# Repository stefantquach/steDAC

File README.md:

# SteDAC

Open source audio DAC project based on the ES9038Q2M DAC from ESS. Still WIP

# Credits
Logo art by @yumightaswell (Instagram)

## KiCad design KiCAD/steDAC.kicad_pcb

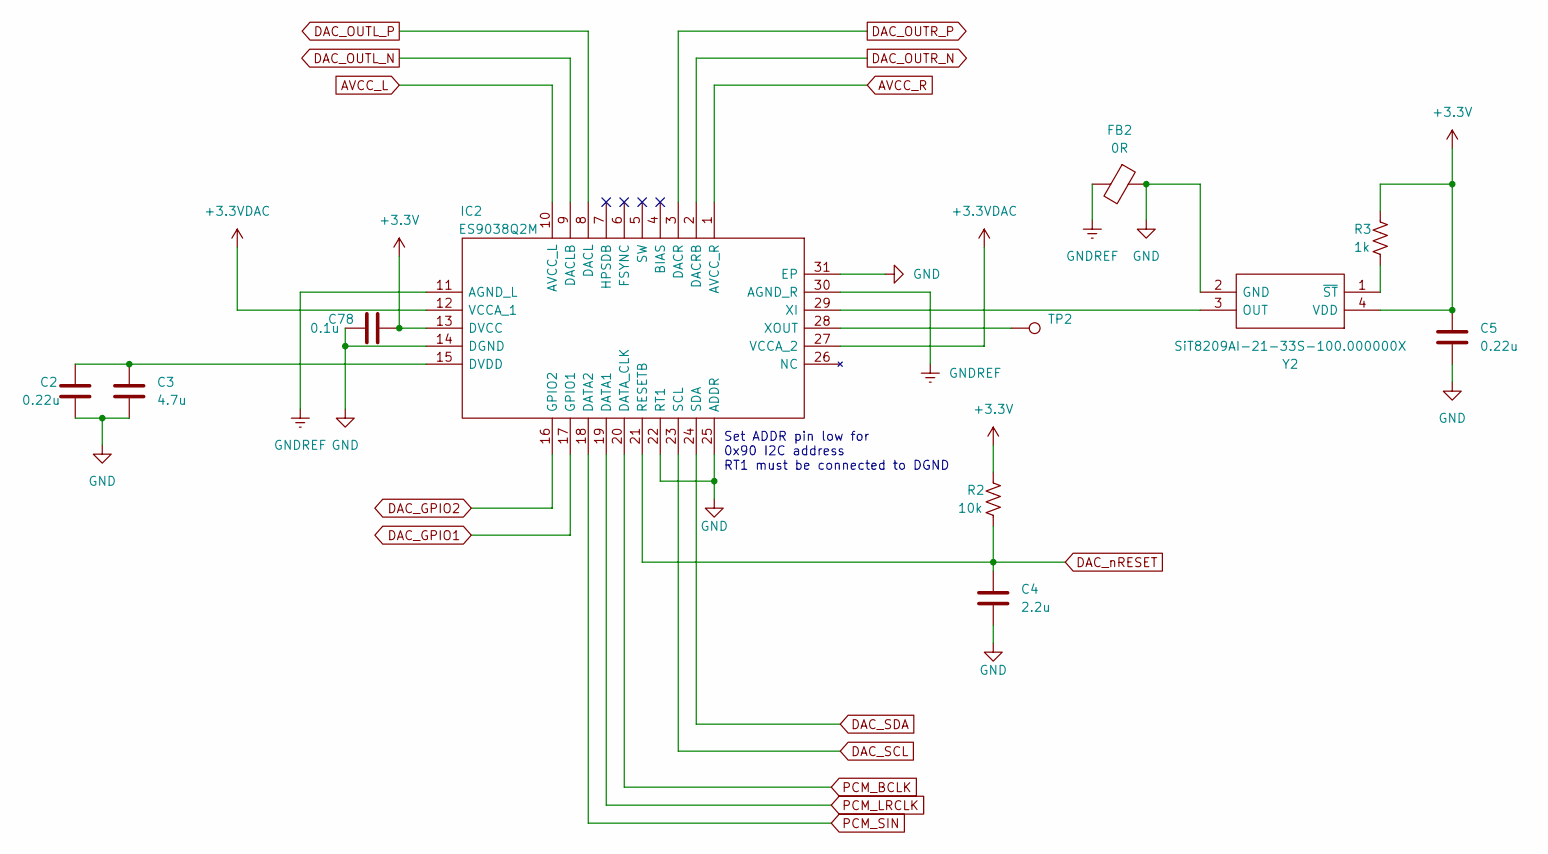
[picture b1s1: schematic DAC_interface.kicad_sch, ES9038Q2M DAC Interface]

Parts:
C2, C5: 0.22u; C_0805_2012Metric_Pad1.18x1.45mm_HandSolder; Part Number CL21B224KAFNNNG; Mouser Part Number 187-CL21B224KAFNNNG
C3: 4.7u; C_0805_2012Metric_Pad1.18x1.45mm_HandSolder; Part Number CC0805KKX5R7BB475; Mouser Part Number 603-CC805KKX5R7BB475
C4: 2.2u; C_0805_2012Metric_Pad1.18x1.45mm_HandSolder; Part Number TMK212B7225KGHT; Mouser Part Number 963-TMK212B7225KGHT
C78: 0.1u; C_0805_2012Metric_Pad1.18x1.45mm_HandSolder; Part Number CL21B104KBCNFNC; Mouser Part Number 187-CL21B104KBCNFNC
FB2: 0R; BEADC2012X110N; Part Number MFBW1V2012-000-R; Mouser Part Number 704-MFBW1V2012-000-R
IC2: ES9038Q2M; QFN40P300X500X80-31N-D; Manufacturer_Part_Number ES9038Q2M; Mouser Part Number 460-ES9038Q2M
R2: 10k; R_0805_2012Metric_Pad1.20x1.40mm_HandSolder; Part Number RC0805FR-7W10KL; Mouser Part Number 603-RC0805FR-7W10KL
R3: 1k; R_0805_2012Metric_Pad1.20x1.40mm_HandSolder; Part Number ERJ-HP6D1001V; Mouser Part Number 667-ERJ-HP6D1001V
TP2: TestPoint; TestPoint_Pad_D1.0mm
Y2: SiT8209AI-21-33S-100.000000X; SiT8209AI2133S100000000X; Manufacturer_Part_Number SiT8209AI-21-33S-100.000000X; Mouser Part Number 788-8209AI2133S-100X

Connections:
+3.3VDAC: IC2.12 (VCCA_1), IC2.27 (VCCA_2); also elsewhere on the board
+3V3: C5.1, C78.1, IC2.13 (DVCC), R2.1, R3.1, Y2.4 (VDD); also elsewhere on the board
AVCC_L: IC2.10 (AVCC_L); also elsewhere on the board
AVCC_R: IC2.1 (AVCC_R); also elsewhere on the board
DAC_GPIO1: IC2.17 (GPIO1); also elsewhere on the board
DAC_GPIO2: IC2.16 (GPIO2); also elsewhere on the board
DAC_OUTL_N: IC2.9 (DACLB); also elsewhere on the board
DAC_OUTL_P: IC2.8 (DACL); also elsewhere on the board
DAC_OUTR_N: IC2.2 (DACRB); also elsewhere on the board
DAC_OUTR_P: IC2.3 (DACR); also elsewhere on the board
DAC_SCL: IC2.23 (SCL); also elsewhere on the board
DAC_SDA: IC2.24 (SDA); also elsewhere on the board
DAC_nRESET: C4.1, IC2.21 (RESETB), R2.2; also elsewhere on the board
GND: C2.2, C3.2, C4.2, C5.2, C78.2, FB2.1, IC2.14 (DGND), IC2.22 (RT1), IC2.25 (ADDR), IC2.31 (EP), Y2.2 (GND); also elsewhere on the board
GNDREF: FB2.2, IC2.11 (AGND_L), IC2.30 (AGND_R); also elsewhere on the board
unnamed: C2.1, C3.1, IC2.15 (DVDD)
unnamed: IC2.28 (XOUT), TP2.1
unnamed: IC2.29 (XI), Y2.3 (OUT)
unnamed: R3.2, Y2.1 (~ST)
PCM_BCLK: IC2.20 (DATA_CLK); also elsewhere on the board
PCM_LRCLK: IC2.19 (DATA1); also elsewhere on the board
PCM_SIN: IC2.18 (DATA2); also elsewhere on the board

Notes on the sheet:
Set ADDR pin low for 0x90 I2C address RT1 must be connected to DGND

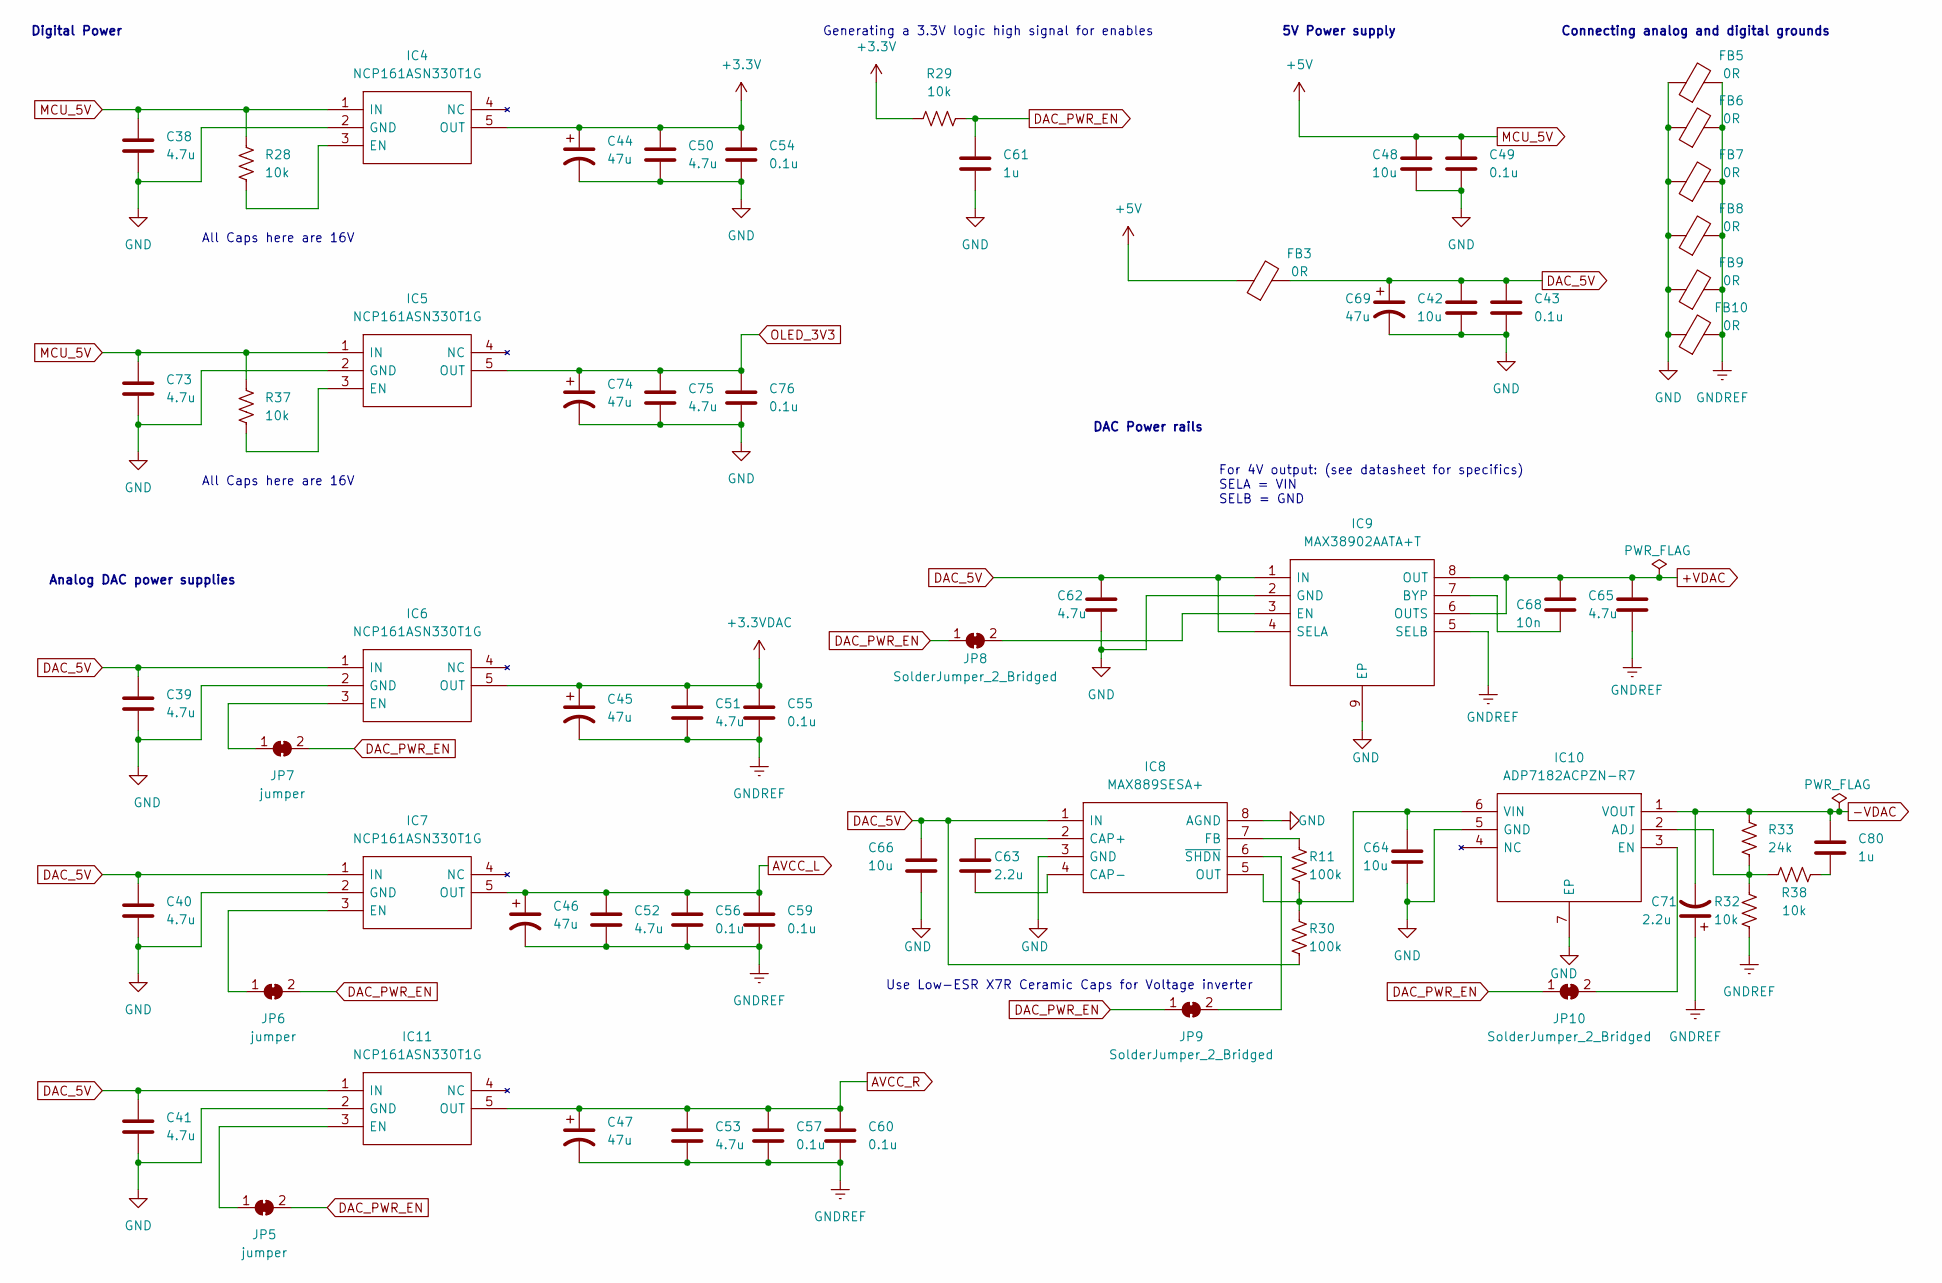
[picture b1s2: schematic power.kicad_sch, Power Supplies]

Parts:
C38, C39, C40, C41, C50, C51, C52, C53, C62, C65, C73, C75: 4.7u; C_0805_2012Metric_Pad1.18x1.45mm_HandSolder; Part Number CC0805KKX5R7BB475; Mouser Part Number 603-CC805KKX5R7BB475
C42, C48, C64, C66: 10u; C_0805_2012Metric_Pad1.18x1.45mm_HandSolder; Part Number TMK212BBJ106KG-T; Mouser Part Number 963-TMK212BBJ106KG-T
C43, C49, C54, C55, C56, C57, C59, C60, C76: 0.1u; C_0805_2012Metric_Pad1.18x1.45mm_HandSolder; Part Number CL21B104KBCNFNC; Mouser Part Number 187-CL21B104KBCNFNC
C44, C45, C46, C47, C69, C74: 47u; CP_Radial_D5.0mm_P2.50mm; Part Number ECA-1CHG470I; Mouser Part Number 667-ECA-1CHG470I
C61: 1u; C_0805_2012Metric_Pad1.18x1.45mm_HandSolder; Part Number EMK212B7105KG-T; Mouser Part Number 963-EMK212B7105KG-T
C63: 2.2u; C_0805_2012Metric_Pad1.18x1.45mm_HandSolder; Part Number TMK212B7225KGHT; Mouser Part Number 963-TMK212B7225KGHT
C68: 10n; C_0805_2012Metric_Pad1.18x1.45mm_HandSolder; Part Number C0805C103K4RECTU; Mouser Part Number 80-C0805C103K4RECTU
C71: 2.2u; CP_Radial_D4.0mm_P1.50mm; Part Number ECE-A1HKA2R2; Mouser Part Number 667-ECE-A1HKA2R2
C80: 1u; C_0805_2012Metric_Pad1.18x1.45mm_HandSolder; Mouser Part Number 963-EMK212B7105KG-T
FB3, FB5, FB6, FB7, FB8, FB9, FB10: 0R; BEADC2012X110N; Part Number MFBW1V2012-000-R; Mouser Part Number 704-MFBW1V2012-000-R
IC4, IC5, IC6, IC7, IC11: NCP161ASN330T1G; SOT95P280X145-5N; Manufacturer_Part_Number NCP161ASN330T1G; Mouser Part Number 863-NCP161ASN330T1G
IC8: MAX889SESA+; SOIC127P600X175-8N; Manufacturer_Part_Number MAX889SESA+; Mouser Part Number 700-MAX889SESA
IC9: MAX38902AATA+T; SON50P200X200X80-9N-D; Manufacturer_Part_Number MAX38902AATA+T; Mouser Part Number 700-MAX38902AATA+T
IC10: ADP7182ACPZN-R7; SON65P200X200X65-7N-D; Manufacturer_Part_Number ADP7182ACPZN-R7; Mouser Part Number 584-ADP7182ACPZN-R7
JP5, JP6, JP7: jumper; SolderJumper-2_P1.3mm_Bridged2Bar_Pad1.0x1.5mm
JP8, JP9, JP10: SolderJumper_2_Bridged; SolderJumper-2_P1.3mm_Bridged2Bar_Pad1.0x1.5mm
R11, R30: 100k; R_0805_2012Metric_Pad1.20x1.40mm_HandSolder; Part Number RCV0805100KJNEA; Mouser Part Number 71-RCV0805100KJNEA
R28, R29, R37: 10k; R_0805_2012Metric_Pad1.20x1.40mm_HandSolder; Part Number RC0805FR-7W10KL; Mouser Part Number 603-RC0805FR-7W10KL
R32, R38: 10k; R_0805_2012Metric_Pad1.20x1.40mm_HandSolder; Part Number RT0805BRD0710KL; Mouser Part Number 603-RT0805BRD0710KL
R33: 24k; R_0805_2012Metric_Pad1.20x1.40mm_HandSolder; Part Number ERA-6AEB243V; Mouser Part Number 667-ERA-6AEB243V

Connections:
+3.3VDAC: C45.1, C51.1, C55.1, IC6.5 (OUT); also elsewhere on the board
+3V3: C44.1, C50.1, C54.1, IC4.5 (OUT), R29.1; also elsewhere on the board
+VDAC: C65.1, C68.1, IC9.6 (OUTS), IC9.8 (OUT); also elsewhere on the board
-VDAC: C71.2, C80.1, IC10.1 (VOUT), R33.2; also elsewhere on the board
AVCC_L: C46.1, C52.1, C56.1, C59.1, IC7.5 (OUT); also elsewhere on the board
AVCC_R: C47.1, C53.1, C57.1, C60.1, IC11.5 (OUT); also elsewhere on the board
DAC_5V: C39.1, C40.1, C41.1, C42.2, C43.1, C62.1, C66.1, C69.1, FB3.2, IC6.1 (IN), IC7.1 (IN), IC8.1 (IN), IC9.1 (IN), IC9.4 (SELA), IC11.1 (IN), R30.1
DAC_PWR_EN: C61.1, JP5.2 (B), JP6.2 (B), JP7.2 (B), JP8.1 (A), JP9.1 (A), JP10.1 (A), R29.2
GND: C38.2, C39.2, C40.2, C41.2, C42.1, C43.2, C44.2, C48.1, C49.2, C50.2, C54.2, C61.2, C62.2, C64.2, C66.2, C69.2, C73.2, C74.2, C75.2, C76.2, FB5.1, FB6.1, FB7.1, FB8.1, FB9.1, FB10.1, IC4.2 (GND), IC5.2 (GND), IC6.2 (GND), IC7.2 (GND), IC8.3 (GND), IC8.8 (AGND), IC9.2 (GND), IC9.9 (EP), IC10.5 (GND), IC10.7 (EP), IC11.2 (GND); also elsewhere on the board
GNDREF: C45.2, C46.2, C47.2, C51.2, C52.2, C53.2, C55.2, C56.2, C57.2, C59.2, C60.2, C65.2, C71.1, FB5.2, FB6.2, FB7.2, FB8.2, FB9.2, FB10.2, IC9.5 (SELB), R32.1; also elsewhere on the board
MCU_5V: C38.1, C48.2, C49.1, C73.1, FB3.1, IC4.1 (IN), IC5.1 (IN), R28.2, R37.2; also elsewhere on the board
unnamed: C63.1, IC8.2 (CAP+)
unnamed: C63.2, IC8.4 (CAP-)
unnamed: C64.1, IC8.5 (OUT), IC10.6 (VIN), R11.1, R30.2
unnamed: C68.2, IC9.7 (BYP)
unnamed: C80.2, R38.1
unnamed: IC4.3 (EN), R28.1
unnamed: IC5.3 (EN), R37.1
unnamed: IC6.3 (EN), JP7.1 (A)
unnamed: IC7.3 (EN), JP6.1 (A)
unnamed: IC8.6 (~SHDN), JP9.2 (B)
unnamed: IC8.7 (FB), R11.2
unnamed: IC9.3 (EN), JP8.2 (B)
unnamed: IC10.2 (ADJ), R32.2, R33.1, R38.2
unnamed: IC10.3 (EN), JP10.2 (B)
unnamed: IC11.3 (EN), JP5.1 (A)
OLED_3V3: C74.1, C75.1, C76.1, IC5.5 (OUT); also elsewhere on the board

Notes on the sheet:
DAC Power rails
Connecting analog and digital grounds
For 4V output: (see datasheet for specifics) SELA = VIN SELB = GND
Digital Power
Analog DAC power supplies
Generating a 3.3V logic high signal for enables
Use Low-ESR X7R Ceramic Caps for Voltage inverter
All Caps here are 16V
5V Power supply

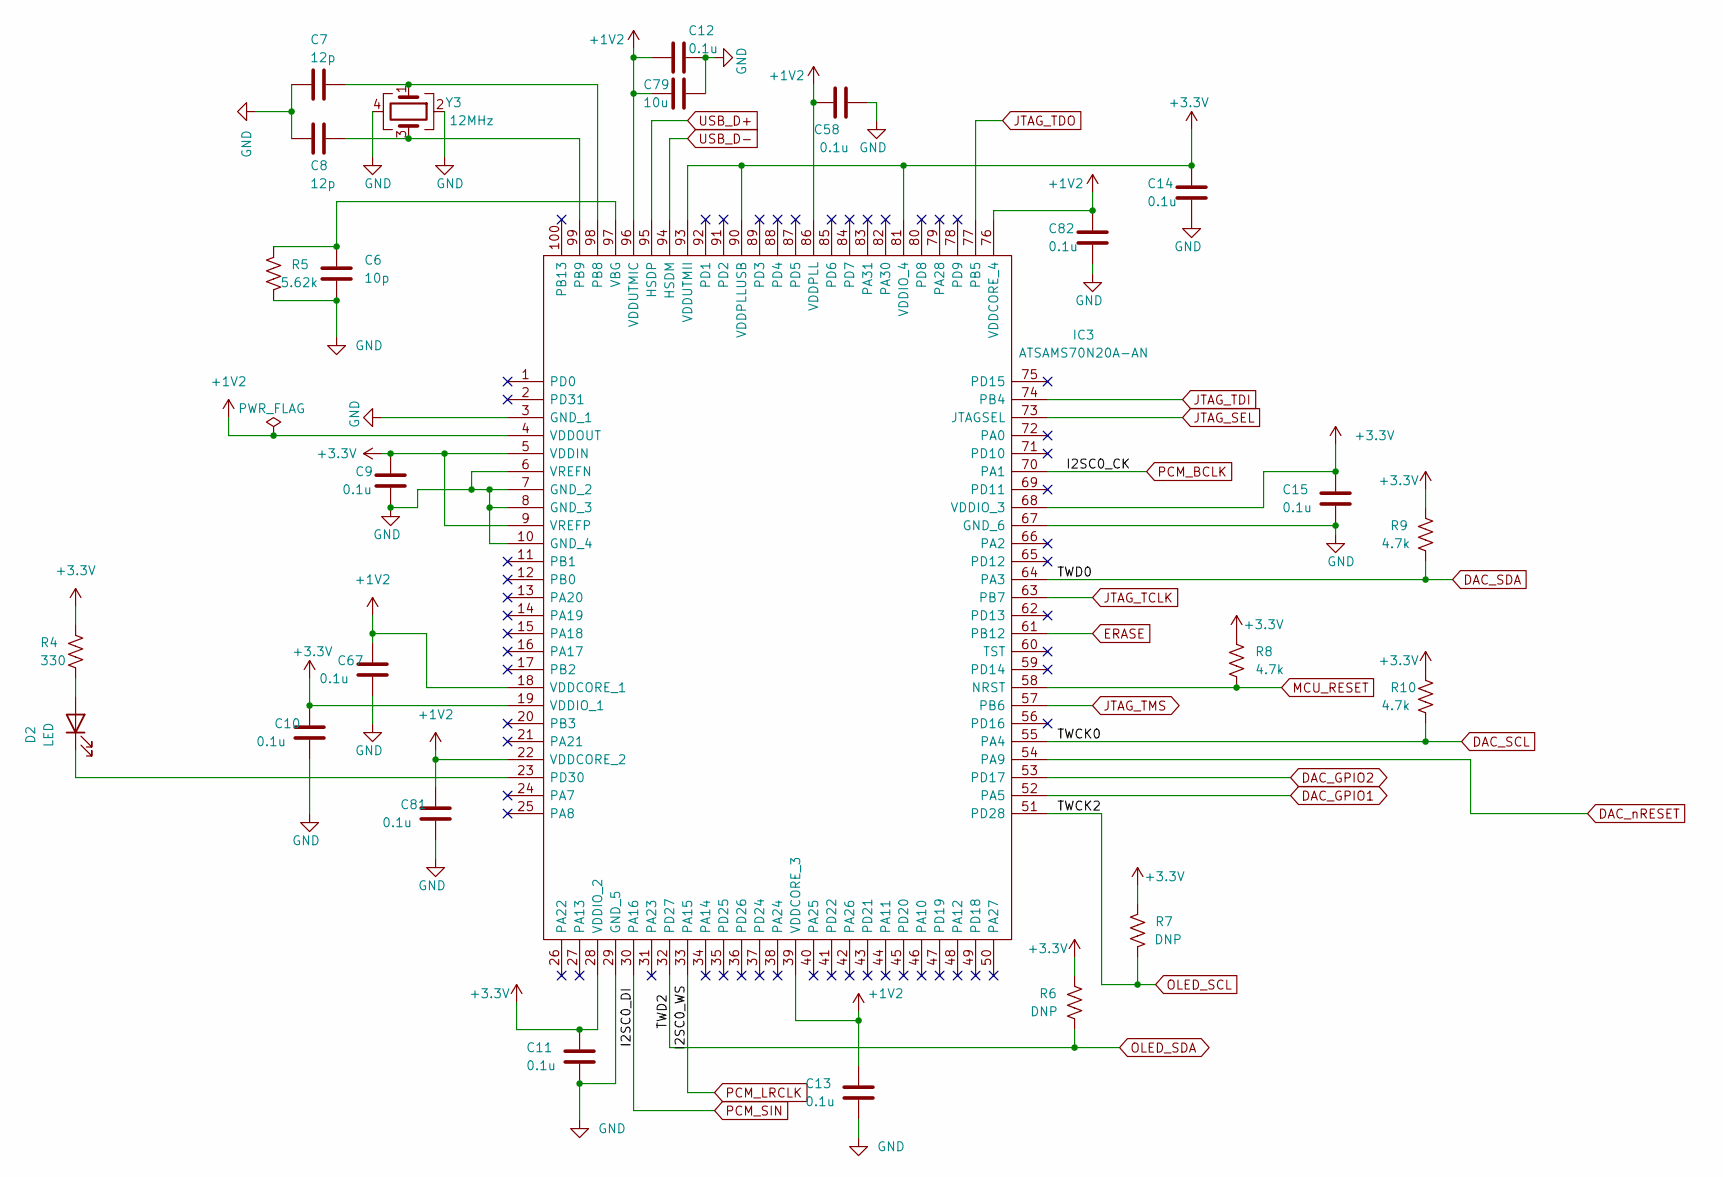
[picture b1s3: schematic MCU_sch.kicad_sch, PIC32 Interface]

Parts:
C6: 10p; C_0805_2012Metric_Pad1.18x1.45mm_HandSolder; Part Number VJ0805A100GXJCW1BC; Mouser Part Number 77-VJ0805A100GXJCBC
C7, C8: 12p; C_0805_2012Metric_Pad1.18x1.45mm_HandSolder; Part Number C0805C120J8GACTU; Mouser Part Number 80-C0805C120J8G
C9, C10, C11, C12, C13, C14, C15, C58, C67, C81, C82: 0.1u; C_0805_2012Metric_Pad1.18x1.45mm_HandSolder; Part Number CL21B104KBCNFNC; Mouser Part Number 187-CL21B104KBCNFNC
C79: 10u; C_0805_2012Metric_Pad1.18x1.45mm_HandSolder; Part Number TMK212BBJ106KG-T; Mouser Part Number 963-TMK212BBJ106KG-T
D2: LED; LED_0805_2012Metric_Pad1.15x1.40mm_HandSolder; Part Number SM0805PGC; Mouser Part Number 749-SM0805PGC
IC3: ATSAMS70N20A-AN; QFP50P1600X1600X160-100N; Manufacturer_Part_Number ATSAMS70N20A-AN; Mouser Part Number 556-ATSAMS70N20A-AN
R4: 330; R_0805_2012Metric_Pad1.20x1.40mm_HandSolder; Part Number CMP0805-FX-3300ELF; Mouser Part Number 652-CMP0805-FX-3300L
R5: 5.62k; R_0805_2012Metric_Pad1.20x1.40mm_HandSolder; Part Number CRCW08055K62FKEAC; Mouser Part Number 71-CRCW08055K62FKEAC
R6, R7: DNP; R_0805_2012Metric_Pad1.20x1.40mm_HandSolder
R8, R9, R10: 4.7k; R_0805_2012Metric_Pad1.20x1.40mm_HandSolder; Part Number ERJ-P06J472V; Mouser Part Number 667-ERJ-P06J472V
Y3: 12MHz; ABM3B; Part Number ABM3B-12.000MHZ-12-N2Y-T; Mouser Part Number 815-ABM3B12MHZ12N2YT

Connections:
+1V2: C12.2, C13.1, C58.1, C67.1, C79.2, C81.1, C82.1, IC3.4 (VDDOUT), IC3.18 (VDDCORE_1), IC3.22 (VDDCORE_2), IC3.39 (VDDCORE_3), IC3.76 (VDDCORE_4), IC3.86 (VDDPLL), IC3.96 (VDDUTMIC)
+3V3: C9.1, C10.1, C11.1, C14.1, C15.1, IC3.5 (VDDIN), IC3.9 (VREFP), IC3.19 (VDDIO_1), IC3.28 (VDDIO_2), IC3.68 (VDDIO_3), IC3.81 (VDDIO_4), IC3.90 (VDDPLLUSB), IC3.93 (VDDUTMII), R4.1, R6.1, R7.1, R8.1, R9.1, R10.1; also elsewhere on the board
DAC_GPIO1: IC3.52 (PA5); also elsewhere on the board
DAC_GPIO2: IC3.53 (PD17); also elsewhere on the board
DAC_SCL: IC3.55 (PA4), R10.2; also elsewhere on the board
DAC_SDA: IC3.64 (PA3), R9.2; also elsewhere on the board
DAC_nRESET: IC3.54 (PA9); also elsewhere on the board
ERASE: IC3.61 (PB12); also elsewhere on the board
GND: C6.2, C7.2, C8.2, C9.2, C10.2, C11.2, C12.1, C13.2, C14.2, C15.2, C58.2, C67.2, C79.1, C81.2, C82.2, IC3.3 (GND_1), IC3.6 (VREFN), IC3.7 (GND_2), IC3.8 (GND_3), IC3.10 (GND_4), IC3.29 (GND_5), IC3.67 (GND_6), R5.2, Y3.2, Y3.4; also elsewhere on the board
JTAG_SEL: IC3.73 (JTAGSEL); also elsewhere on the board
JTAG_TCLK: IC3.63 (PB7); also elsewhere on the board
JTAG_TDI: IC3.74 (PB4); also elsewhere on the board
JTAG_TDO: IC3.77 (PB5); also elsewhere on the board
JTAG_TMS: IC3.57 (PB6); also elsewhere on the board
MCU_RESET: IC3.58 (NRST), R8.2; also elsewhere on the board
unnamed: C6.1, IC3.97 (VBG), R5.1
unnamed: C7.1, IC3.98 (PB8), Y3.1
unnamed: C8.1, IC3.99 (PB9), Y3.3
unnamed: D2.1 (K), IC3.23 (PD30)
unnamed: D2.2 (A), R4.2
OLED_SCL: IC3.51 (PD28), R7.2; also elsewhere on the board
OLED_SDA: IC3.32 (PD27), R6.2; also elsewhere on the board
PCM_BCLK: IC3.70 (PA1); also elsewhere on the board
PCM_LRCLK: IC3.33 (PA15); also elsewhere on the board
PCM_SIN: IC3.30 (PA16); also elsewhere on the board
USB_D+: IC3.95 (HSDP); also elsewhere on the board
USB_D-: IC3.94 (HSDM); also elsewhere on the board

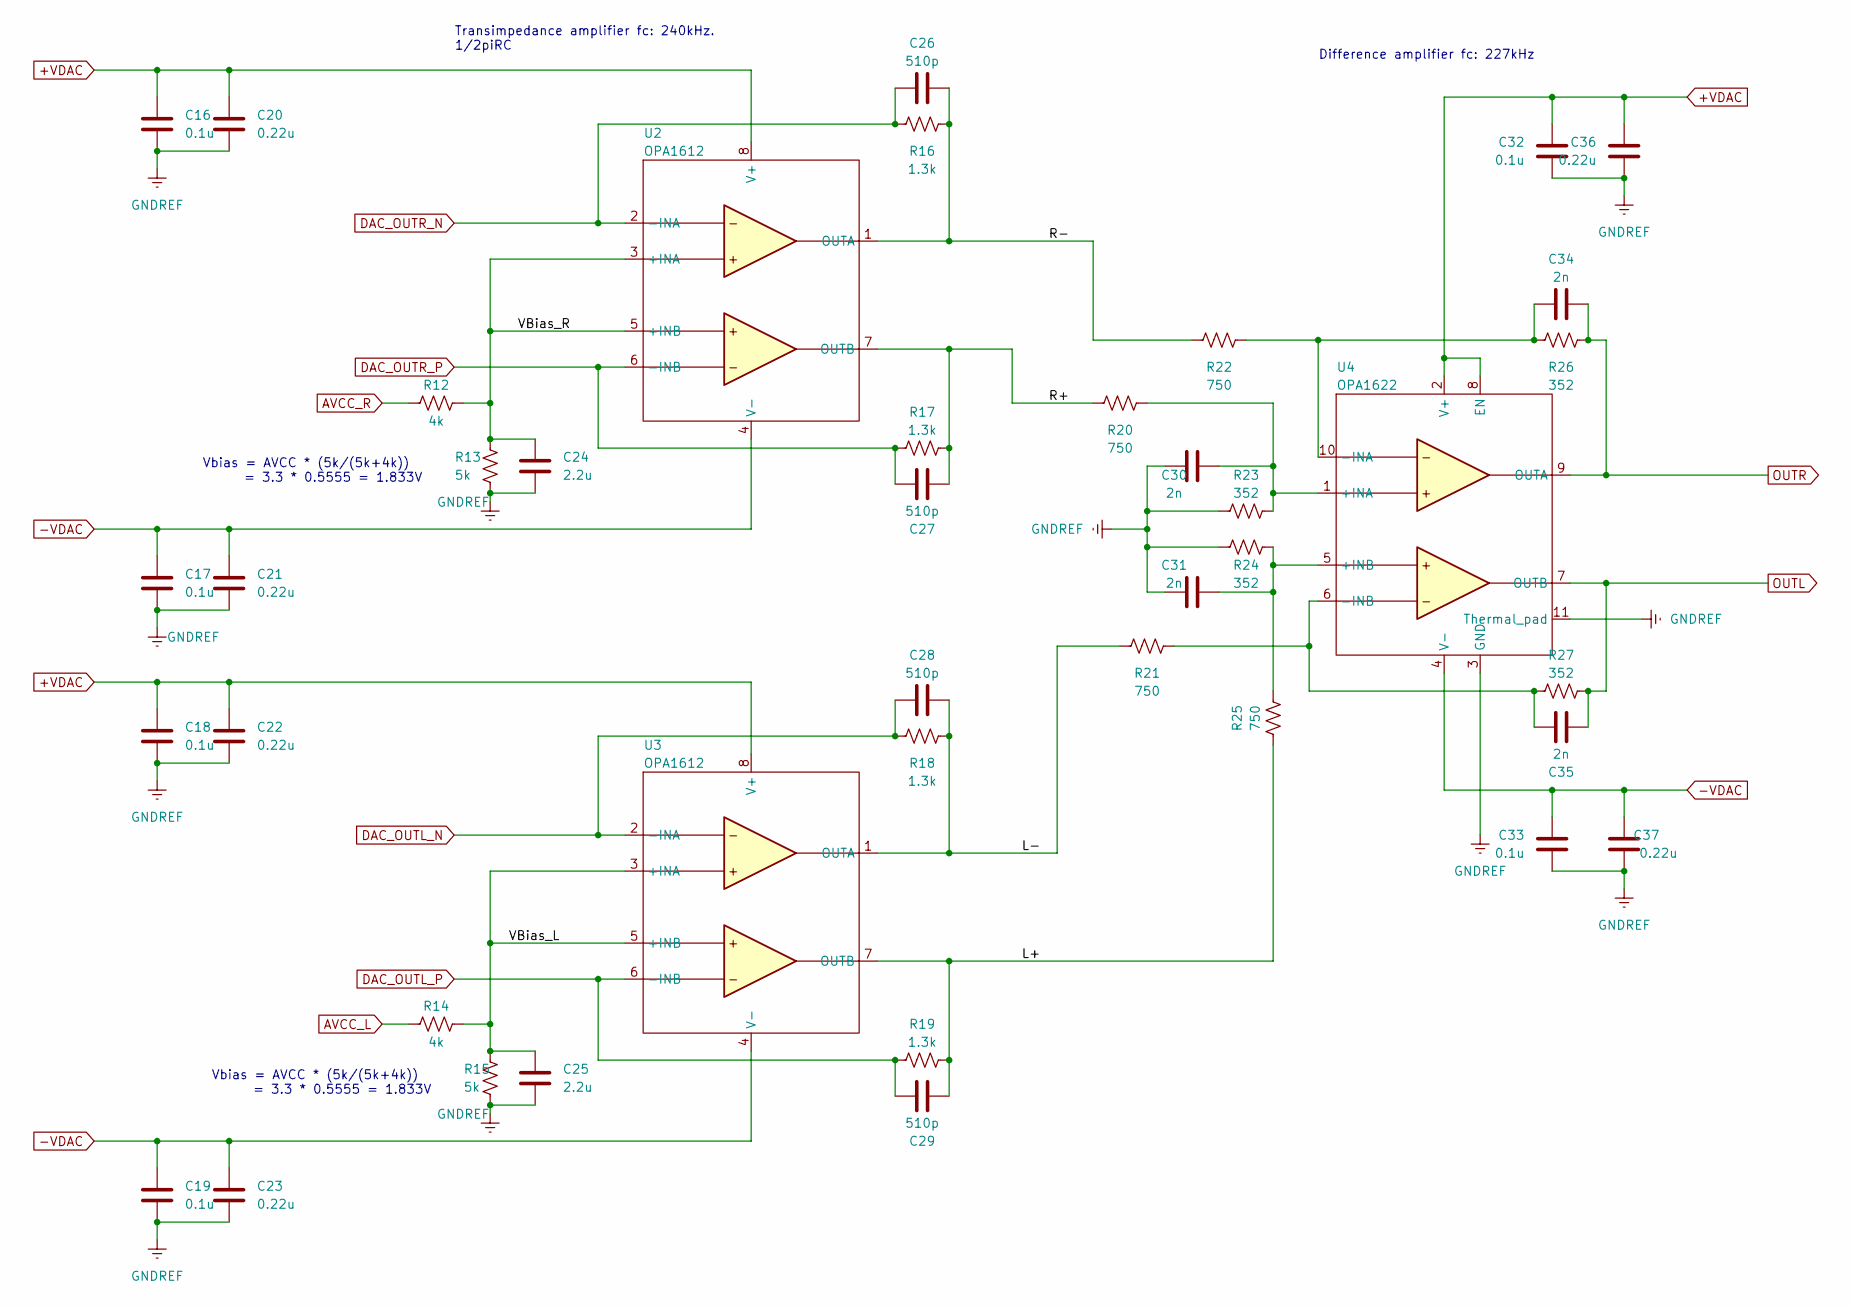
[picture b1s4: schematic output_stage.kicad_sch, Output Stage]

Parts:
C16, C17, C18, C19: 0.1u; C_0805_2012Metric_Pad1.18x1.45mm_HandSolder; Part Number CL21B104KBCNFNC; Mouser Part Number 187-CL21B104KBCNFNC
C20, C21, C22, C23, C36, C37: 0.22u; C_0805_2012Metric_Pad1.18x1.45mm_HandSolder; Part Number CL21B224KAFNNNG; Mouser Part Number 187-CL21B224KAFNNNG
C24, C25: 2.2u; C_0805_2012Metric_Pad1.18x1.45mm_HandSolder; Part Number TMK212B7225KGHT; Mouser Part Number 963-TMK212B7225KGHT
C26, C27, C28, C29: 510p; C_0805_2012Metric_Pad1.18x1.45mm_HandSolder; Part Number C0805C511F3HACTU; Mouser Part Number 80-C0805C511F3HACTU
C30, C31, C34, C35: 2n; C_0805_2012Metric_Pad1.18x1.45mm_HandSolder; Part Number C0805C202F4HACAUTO; Mouser Part Number 80-C0805C202F4HAUTO
C32, C33: 0.1u; C_0805_2012Metric_Pad1.18x1.45mm_HandSolder; Mouser Part Number 187-CL21B104KBCNFNC
R12, R14: 4k; R_0805_2012Metric_Pad1.20x1.40mm_HandSolder; Part Number TNPW08054K02BYEN; Mouser Part Number 71-TNPW08054K02BYEN
R13, R15: 5k; R_0805_2012Metric_Pad1.20x1.40mm_HandSolder; Part Number CRT0805-BY-5001EAS; Mouser Part Number 652-CRT0805BY5001EAS
R16, R17, R18, R19: 1.3k; R_0805_2012Metric_Pad1.20x1.40mm_HandSolder; Part Number RG2012P-132-B-T5; Mouser Part Number 754-RG2012P-132-BT5
R20, R21, R22, R25: 750; R_0805_2012Metric_Pad1.20x1.40mm_HandSolder; Part Number TNPW0805750RBEEA; Mouser Part Number 71-TNPW0805750RBEEA
R23, R24, R26, R27: 352; R_0805_2012Metric_Pad1.20x1.40mm_HandSolder; Part Number RN73H2ATTD3520B25; Mouser Part Number 660-RN73H2ATD3520B25
U2, U3: OPA1612; SOIC127P600X175-8N; Part Number OPA1612AID; Mouser Part Number 595-OPA1612AID
U4: OPA1622; SON50P300X300X100-11N; Manufacturer_Part_Number OPA1622IDRCR; Mouser Part Number 595-OPA1622IDRCR

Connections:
+VDAC: C16.2, C18.2, C20.2, C22.2, C32.2, C36.2, U2.8 (V+), U3.8 (V+), U4.2 (V+), U4.8 (EN); also elsewhere on the board
-VDAC: C17.2, C19.2, C21.2, C23.2, C33.2, C37.2, U2.4 (V-), U3.4 (V-), U4.4 (V-); also elsewhere on the board
/Output Stage/L+: C29.2, R19.2, R25.1, U3.7 (OUTB)
/Output Stage/L-: C28.1, R18.1, R21.2, U3.1 (OUTA)
/Output Stage/R+: C27.2, R17.2, R20.2, U2.7 (OUTB)
/Output Stage/R-: C26.1, R16.1, R22.2, U2.1 (OUTA)
/Output Stage/VBias_L: C25.2, R14.1, R15.2, U3.3 (+INA), U3.5 (+INB)
/Output Stage/VBias_R: C24.2, R12.1, R13.2, U2.3 (+INA), U2.5 (+INB)
AVCC_L: R14.2; also elsewhere on the board
AVCC_R: R12.2; also elsewhere on the board
DAC_OUTL_N: C28.2, R18.2, U3.2 (-INA); also elsewhere on the board
DAC_OUTL_P: C29.1, R19.1, U3.6 (-INB); also elsewhere on the board
DAC_OUTR_N: C26.2, R16.2, U2.2 (-INA); also elsewhere on the board
DAC_OUTR_P: C27.1, R17.1, U2.6 (-INB); also elsewhere on the board
GNDREF: C16.1, C17.1, C18.1, C19.1, C20.1, C21.1, C22.1, C23.1, C24.1, C25.1, C30.2, C31.1, C32.1, C33.1, C36.1, C37.1, R13.1, R15.1, R23.1, R24.2, U4.3 (GND), U4.11 (Thermal_pad); also elsewhere on the board
unnamed: C30.1, R20.1, R23.2, U4.1 (+INA)
unnamed: C31.2, R24.1, R25.2, U4.5 (+INB)
unnamed: C34.2, R22.1, R26.2, U4.10 (-INA)
unnamed: C35.1, R21.1, R27.1, U4.6 (-INB)
OUTL: C35.2, R27.2, U4.7 (OUTB); also elsewhere on the board
OUTR: C34.1, R26.1, U4.9 (OUTA); also elsewhere on the board

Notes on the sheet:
Transimpedance amplifier fc: 240kHz. 1/2piRC
Difference amplifier fc: 227kHz
Vbias = AVCC * (5k/(5k+4k)) = 3.3 * 0.5555 = 1.833V

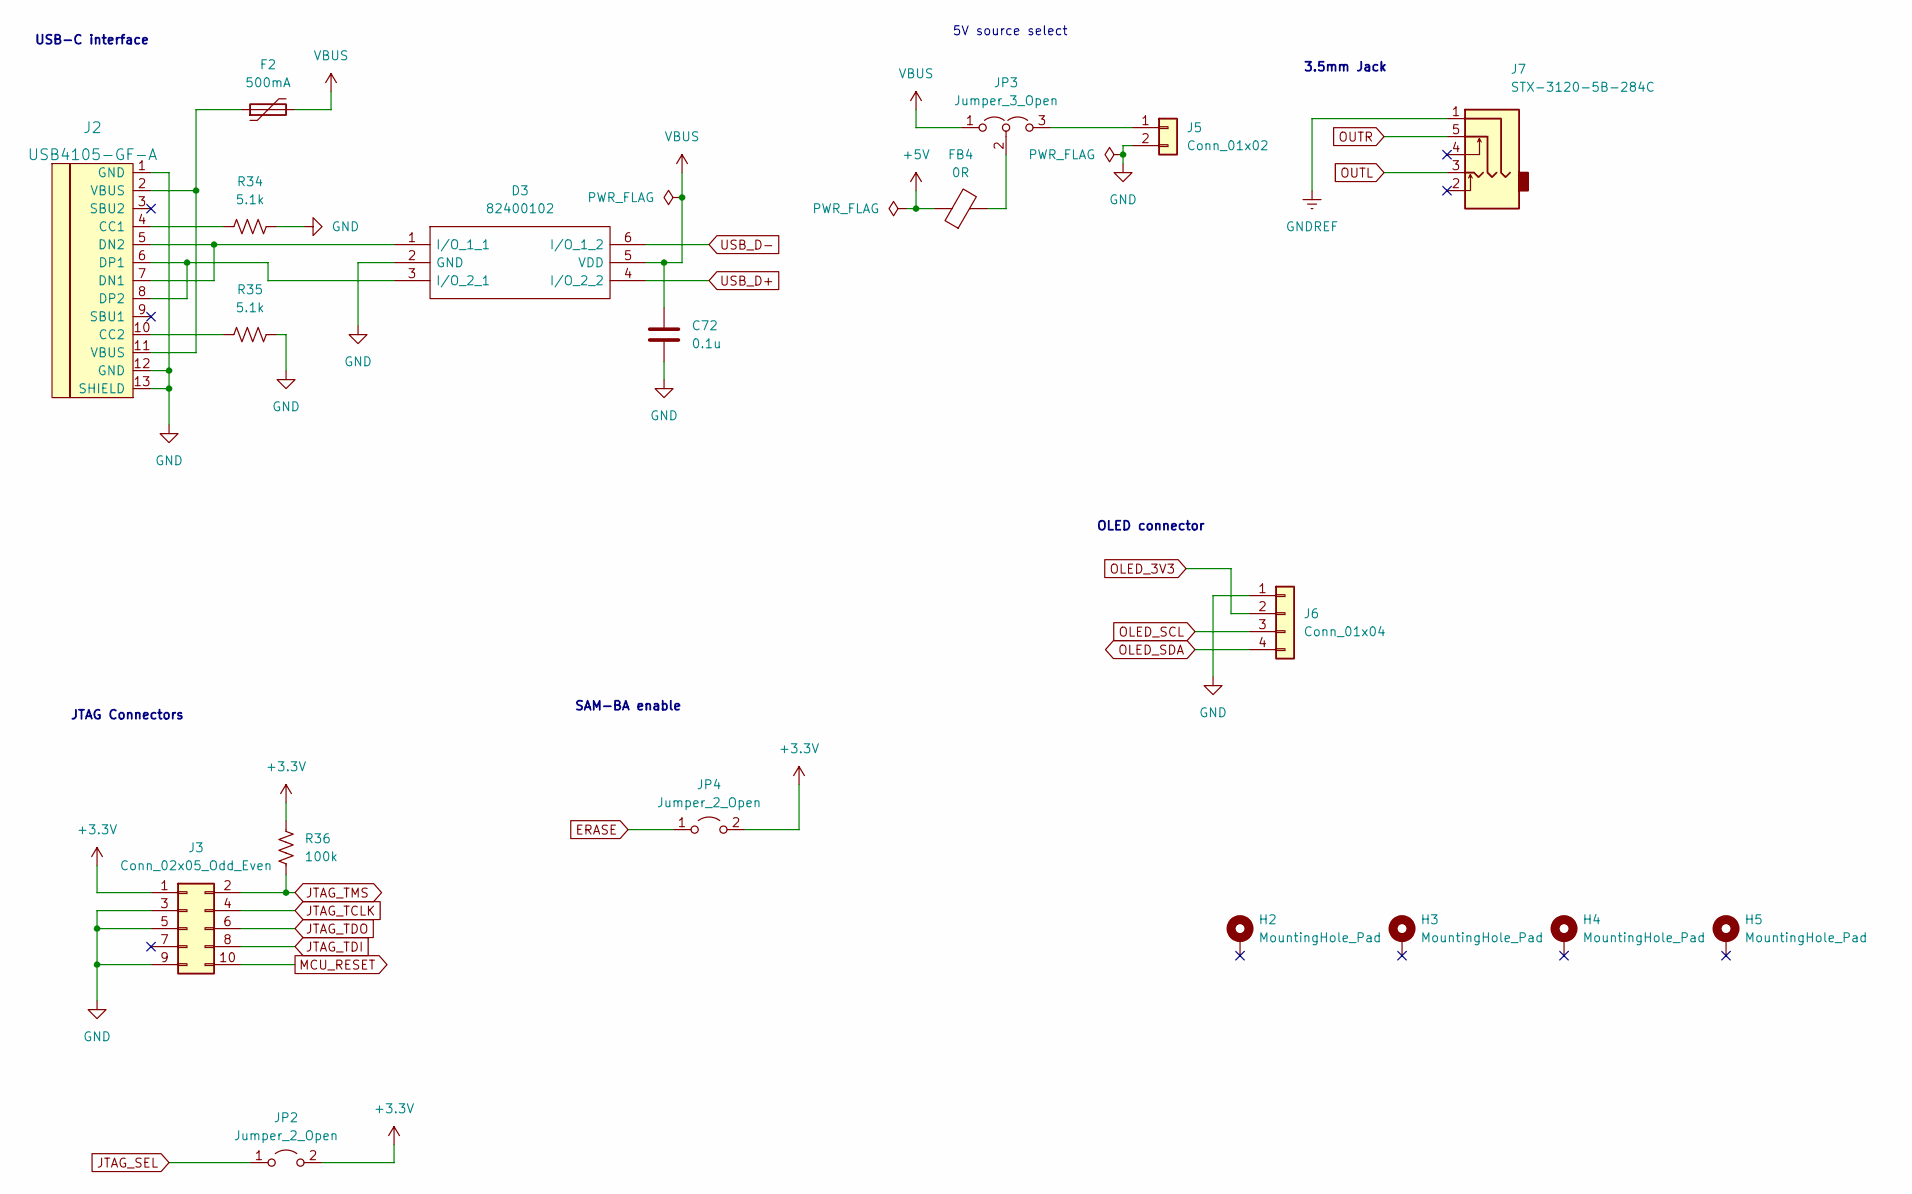
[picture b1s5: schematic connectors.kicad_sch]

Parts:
C72: 0.1u; C_0805_2012Metric_Pad1.18x1.45mm_HandSolder; Part Number CL21B104KBCNFNC; Mouser Part Number 187-CL21B104KBCNFNC
D3: 82400102; SOT95P280X145-6N; Manufacturer_Part_Number 82400102; Mouser Part Number 710-82400102
F2: 500mA; Fuse_1206_3216Metric; Part Number 1206L050/15YR; Mouser Part Number 576-1206L050/15YR
FB4: 0R; BEADC2012X110N; Part Number MFBW1V2012-000-R; Mouser Part Number 704-MFBW1V2012-000-R
H2, H3, H4, H5: MountingHole_Pad; MountingHole_2.2mm_M2_DIN965_Pad_TopBottom
J2: USB4105-GF-A; HRO-TYPE-C-31-M-12-HandSoldering; Part Number USB4105-GF-A; Mouser Part Number 640-USB4105-GF-A
J3: Conn_02x05_Odd_Even; PinHeader_2x05_P2.54mm_Vertical
J5: Conn_01x02; PinHeader_1x02_P2.54mm_Vertical
J6: Conn_01x04; PinHeader_1x04_P2.54mm_Vertical
J7: STX-3120-5B-284C; STX31205B284C; Part Number STX-3120-5B-284C; Mouser Part Number 806-STX-31205B284C
JP2, JP4: Jumper_2_Open; PinHeader_1x02_P2.54mm_Vertical
JP3: Jumper_3_Open; PinHeader_1x03_P2.54mm_Vertical
R34, R35: 5.1k; R_0805_2012Metric_Pad1.20x1.40mm_HandSolder; Part Number ERJ-6RBD5101V; Mouser Part Number 667-ERJ-6RBD5101V
R36: 100k; R_0805_2012Metric_Pad1.20x1.40mm_HandSolder; Part Number RCV0805100KJNEA; Mouser Part Number 71-RCV0805100KJNEA

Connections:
+3V3: J3.1, JP2.2 (B), JP4.2 (B), R36.2; also elsewhere on the board
ERASE: JP4.1 (A); also elsewhere on the board
GND: C72.2, D3.2 (GND), J2.1 (GND), J2.12 (GND), J2.13 (SHIELD), J3.3, J3.5, J3.9, J5.2, J6.1, R34.2, R35.2; also elsewhere on the board
GNDREF: J7.1; also elsewhere on the board
JTAG_SEL: JP2.1 (A); also elsewhere on the board
JTAG_TCLK: J3.4; also elsewhere on the board
JTAG_TDI: J3.8; also elsewhere on the board
JTAG_TDO: J3.6; also elsewhere on the board
JTAG_TMS: J3.2, R36.1; also elsewhere on the board
MCU_5V: FB4.1; also elsewhere on the board
MCU_RESET: J3.10; also elsewhere on the board
unnamed: D3.1 (I/O_1_1), J2.5 (DN2), J2.7 (DN1)
unnamed: D3.3 (I/O_2_1), J2.6 (DP1), J2.8 (DP2)
unnamed: F2.1, J2.2 (VBUS), J2.11 (VBUS)
unnamed: J2.4 (CC1), R34.1
unnamed: J2.10 (CC2), R35.1
unnamed: J5.1, JP3.3 (B)
unnamed: FB4.2, JP3.2 (C)
OLED_3V3: J6.2; also elsewhere on the board
OLED_SCL: J6.3; also elsewhere on the board
OLED_SDA: J6.4; also elsewhere on the board
OUTL: J7.3; also elsewhere on the board
OUTR: J7.5; also elsewhere on the board
USB_D+: D3.4 (I/O_2_2); also elsewhere on the board
USB_D-: D3.6 (I/O_1_2); also elsewhere on the board
VBUS: C72.1, D3.5 (VDD), F2.2, JP3.1 (A)

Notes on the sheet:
OLED connector
SAM-BA enable
JTAG Connectors
USB-C interface
5V source select
3.5mm Jack
